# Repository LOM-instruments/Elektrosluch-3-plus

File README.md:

# Elektrosluch-3+
More info about the device: https://lom.audio/product/elektrosluch-3-plus/

Attached hardware files are made and to be opened with Eagle 7.3, but other versions should work too.

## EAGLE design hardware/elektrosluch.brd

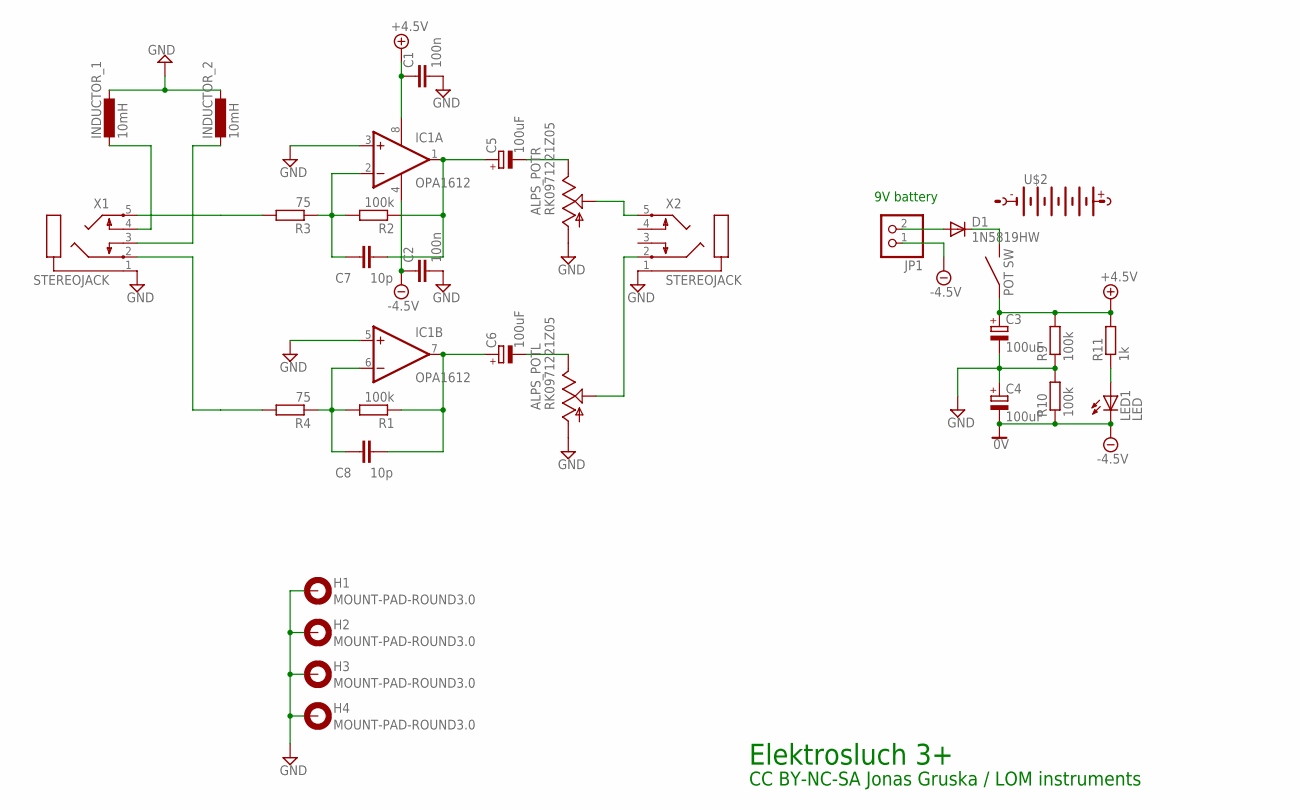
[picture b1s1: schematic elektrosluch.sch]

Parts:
ALPS_POT: RK0971221Z05; ALPS_RK0971221Z0X
C1, C2: 100n; C0603
C3, C4, C5, C6: 100uF; UD-6,3X5,8_NICHICON
C7, C8: 10p; C0603
D1: 1N5819HW; SOD123
H1, H2, H3, H4: MOUNT-PAD-ROUND3.0; 3,0-PAD
IC1: OPA1612; SO08
INDUCTOR_1, INDUCTOR_2: 10mH; COIL
JP1: PINHD-1X2; 1X02
LED1: LED; LED3MM
R1, R2, R9, R10: 100k; R0805
R3, R4: 75; R0805
R11: 1k; R0805
U$2: BATT
X1, X2: STEREOJACK; STX3100

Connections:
+5V: ALPS_POT.S1, C1.1, C3.+, IC1.8 (V+), R9.2, R11.2
-5V: C2.1, C4.-, IC1.4 (V-), JP1.1, LED1.K (C), R10.1
GND: ALPS_POT.G1 (1), ALPS_POT.G2 (1), C1.2, C2.2, C3.-, C4.+, H1.B3,0, H2.B3,0, H3.B3,0, H4.B3,0, IC1.3 (+IN), IC1.5 (+IN), INDUCTOR_1.P$1 (1), INDUCTOR_2.P$1 (1), R9.1, R10.2, X1.1, X2.1
unnamed: C7.1, IC1.2 (-IN), R2.2, R3.1
unnamed: C5.+, C7.2, IC1.1 (OUT), R2.1
unnamed: ALPS_POT.I1 (3), C6.-
unnamed: C8.1, IC1.6 (-IN), R1.2, R4.1
unnamed: C6.+, C8.2, IC1.7 (OUT), R1.1
unnamed: ALPS_POT.I2 (3), C5.-
unnamed: ALPS_POT.O2 (2), X2.5
unnamed: R3.2, X1.5
unnamed: ALPS_POT.O1 (2), X2.2
unnamed: R4.2, X1.2
unnamed: D1.A, JP1.2
unnamed: INDUCTOR_1.P$2 (2), X1.4
unnamed: INDUCTOR_2.P$2 (2), X1.3
unnamed: LED1.A, R11.1
unnamed: ALPS_POT.S2, D1.C

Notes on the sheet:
9V battery
Elektrosluch 3+
CC BY-NC-SA Jonas Gruska / LOM instruments

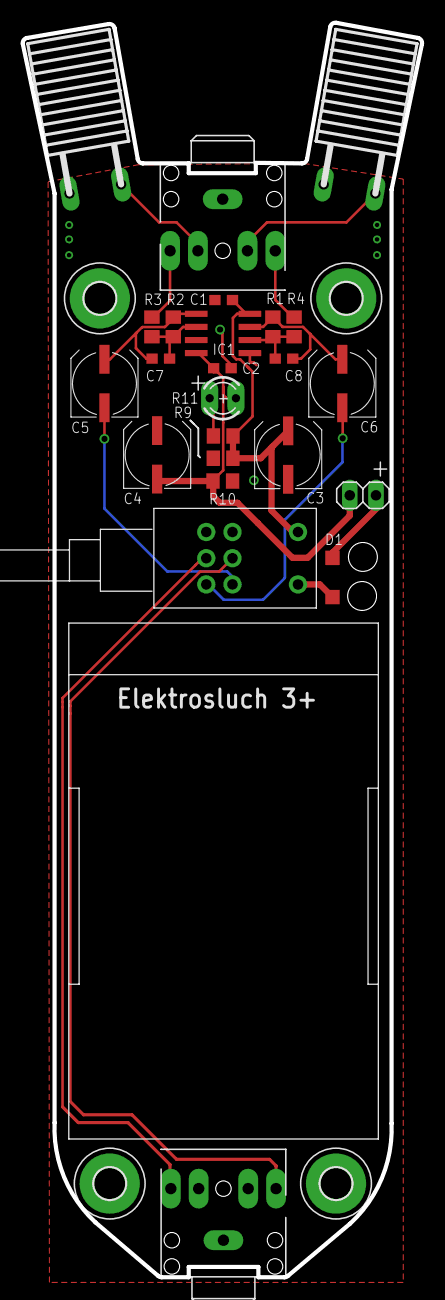
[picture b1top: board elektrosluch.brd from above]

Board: 2 copper layers, 38.7 x 121.6 mm, 30 parts (0 on the bottom side), 18 nets.

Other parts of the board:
U$4: LOM_BACK

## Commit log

2016-09-20 init
